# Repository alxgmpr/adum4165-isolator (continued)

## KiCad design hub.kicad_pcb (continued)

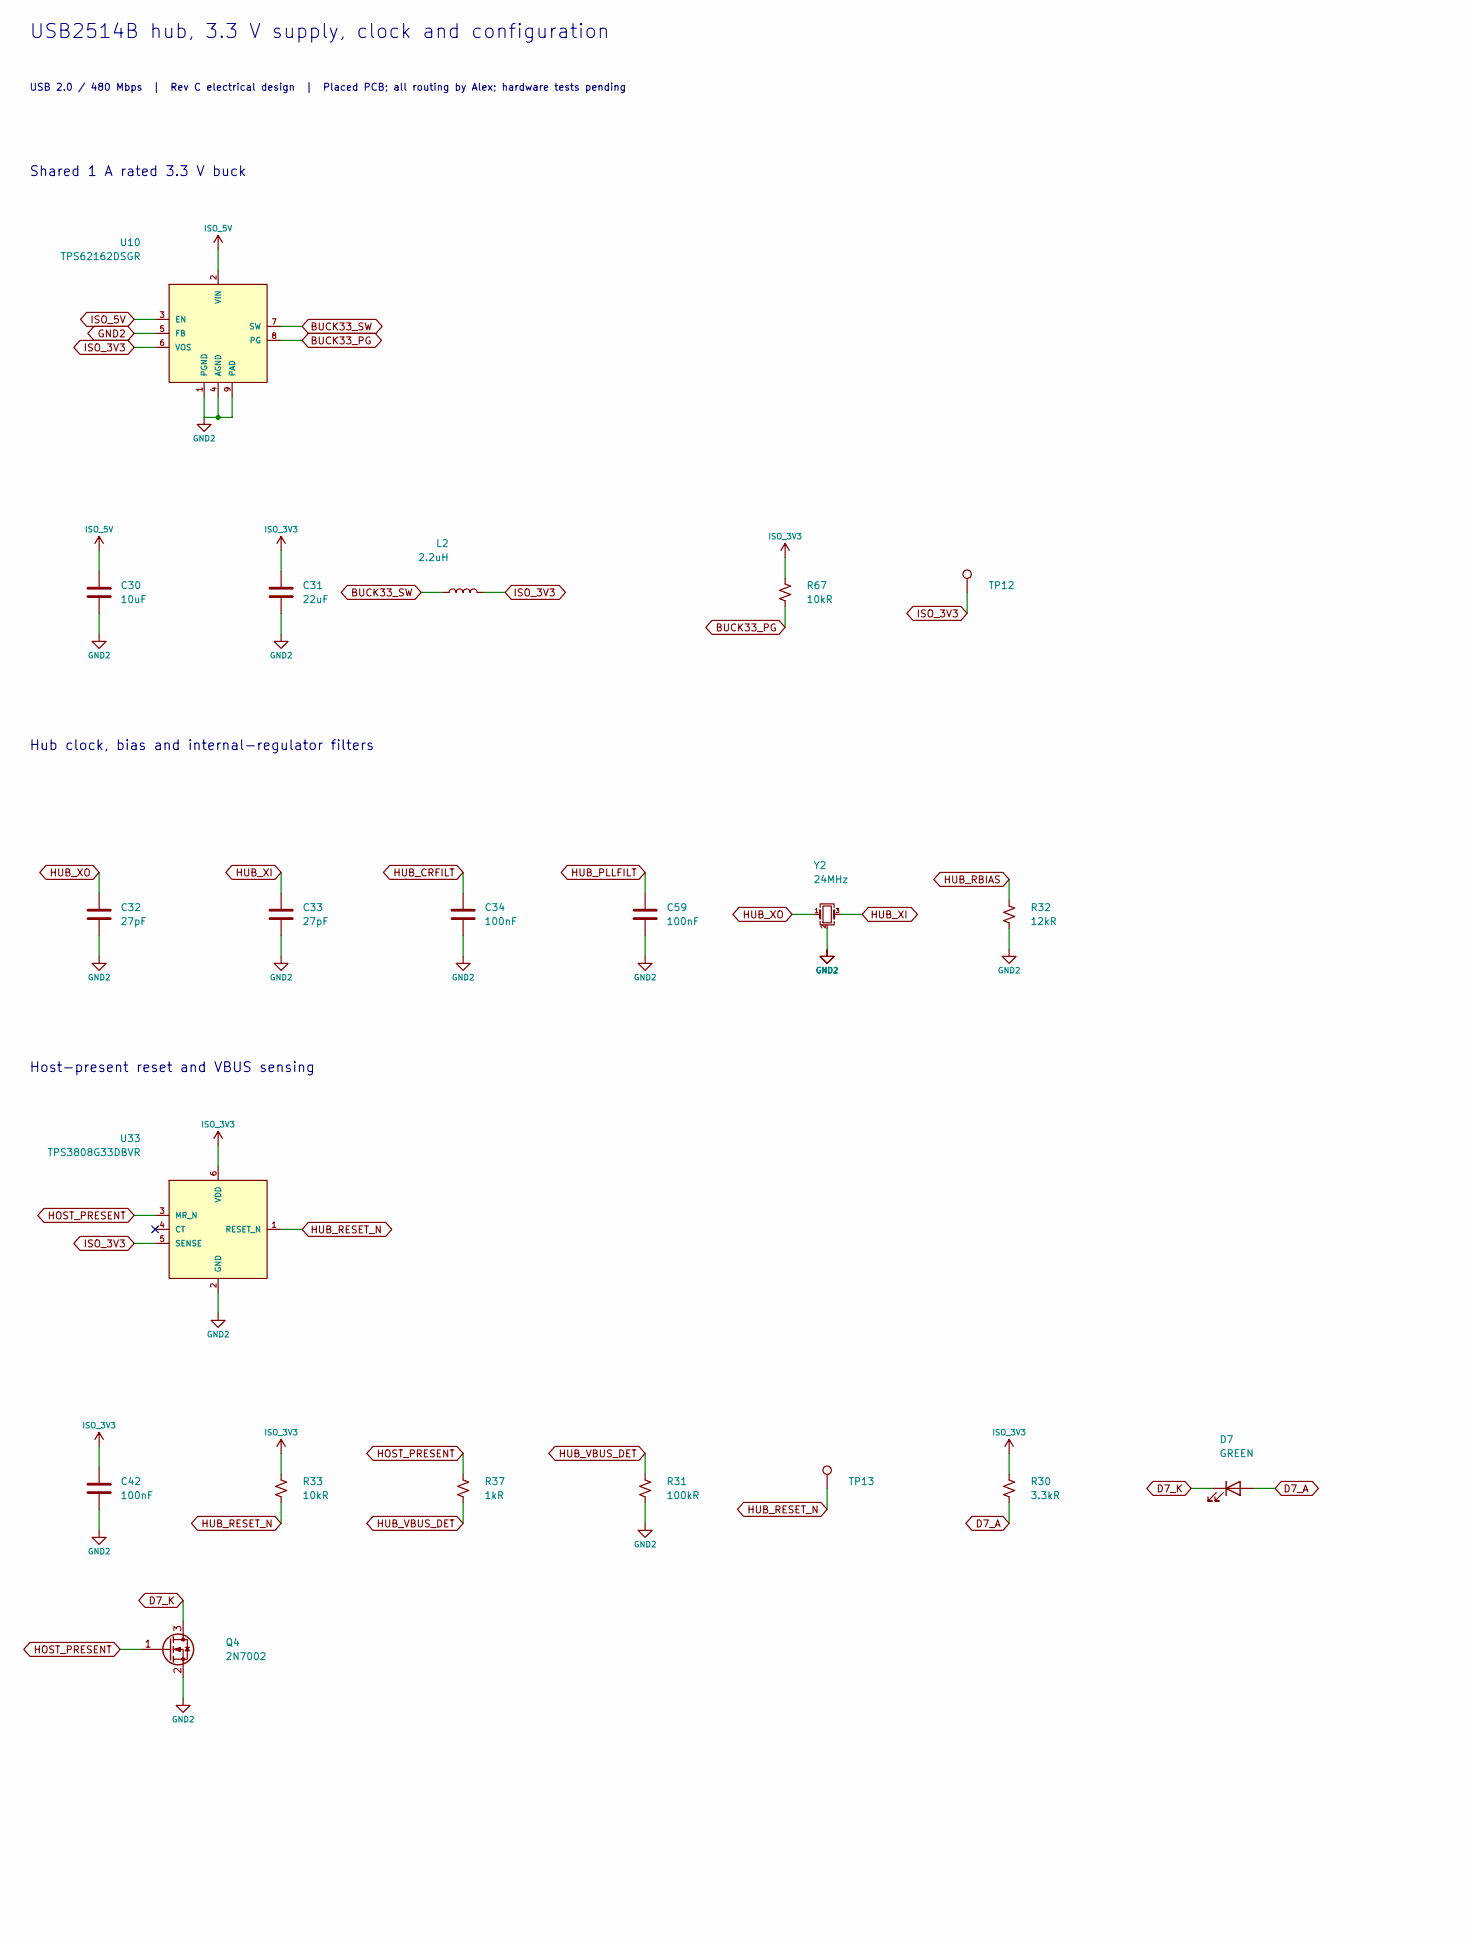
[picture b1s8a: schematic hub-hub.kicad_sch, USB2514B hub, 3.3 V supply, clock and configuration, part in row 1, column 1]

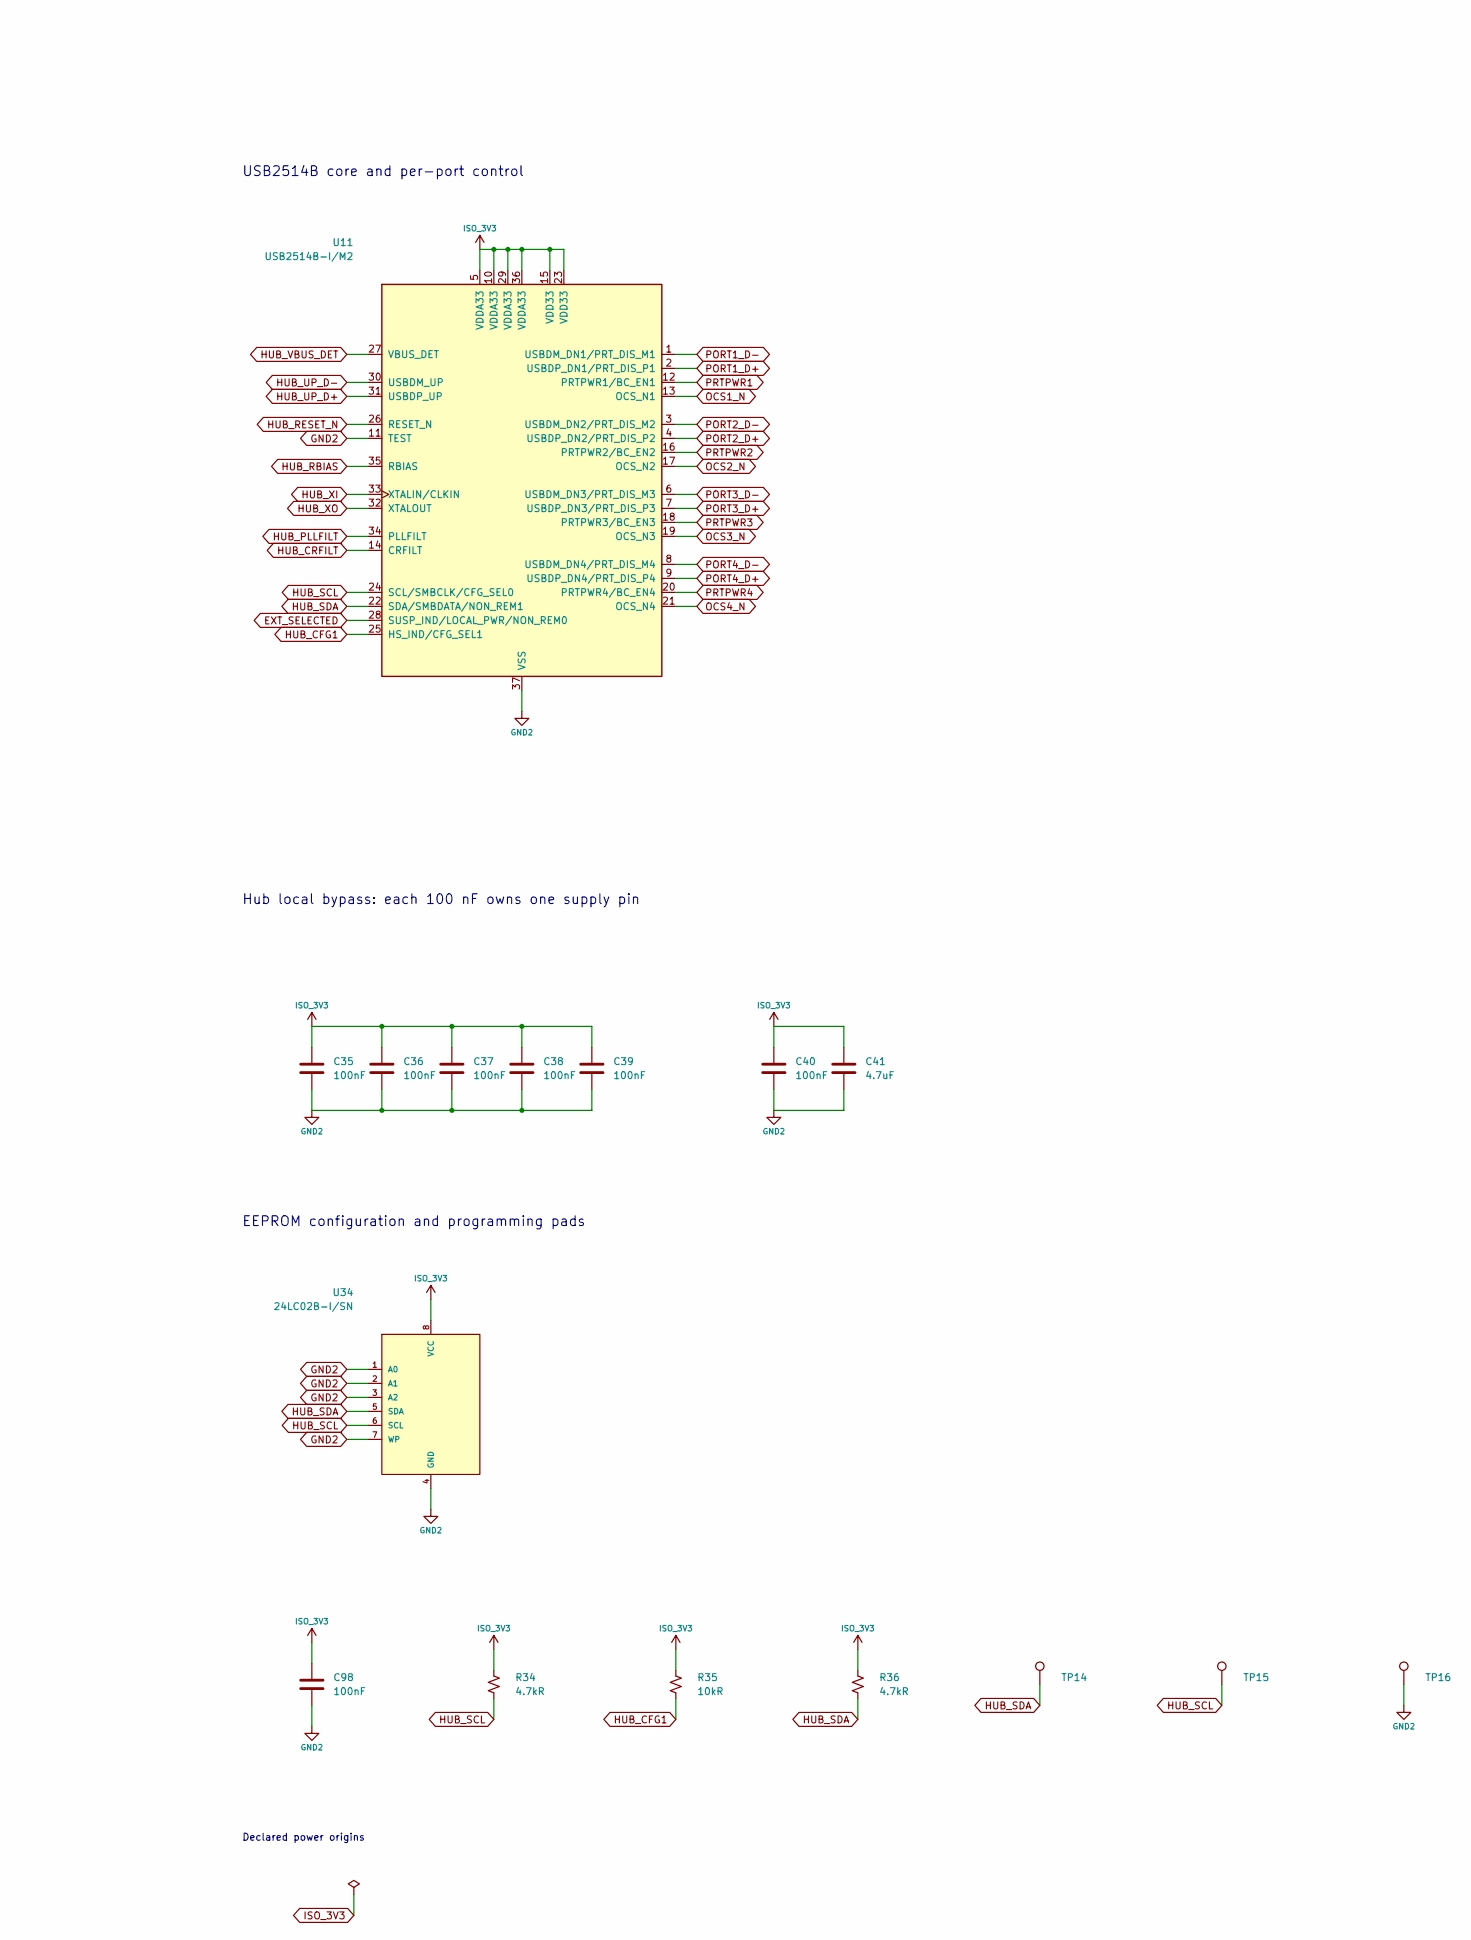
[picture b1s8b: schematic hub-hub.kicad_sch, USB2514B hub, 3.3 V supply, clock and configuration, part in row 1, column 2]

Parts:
C30: 10uF; C_0805_2012Metric; Ratings 25V X5R 10%; MPN GRM21BR61E106KA73L; LCSC C84416
C31: 22uF; C_1210_3225Metric; Ratings 25V X7R 10%; MPN GRM32ER71E226KE15L; LCSC C21397
C32, C33: 27pF; C_0402_1005Metric; Ratings 50V C0G 5%; MPN GCM1555C1H270JA16D; LCSC C126504
C34, C35, C36, C37, C38, C39, C40, C42, C59, C98: 100nF; C_0402_1005Metric; Ratings 50V X7R 10%; MPN GRM155R71H104KE14D; LCSC C77020
C41: 4.7uF; C_0603_1608Metric; Ratings 25V X5R 10%; MPN GRM188R61E475KE11D; LCSC C90057
D7: GREEN; LED_0603_1608Metric; Ratings See exact manufacturer datasheet; MPN LTST-C190KGKT; LCSC C125094
L2: 2.2uH; Coilcraft_XFL4020_4x4mm; Ratings See exact manufacturer datasheet; MPN XFL4020-222MEC; LCSC C122469
Q4: 2N7002; SOT-23; Ratings See exact manufacturer datasheet; MPN 2N7002,215; LCSC C65189
R30: 3.3kR; R_0402_1005Metric; Ratings 1%, 0.1W, 50V; MPN ERJ2RKF3301X; LCSC C409909
R31: 100kR; R_0402_1005Metric; Ratings 1%, 0.1W, 50V; MPN ERJ2RKF1003X; LCSC C192169
R32: 12kR; R_0402_1005Metric; Ratings 1%, 0.1W, 50V; MPN ERJ2RKF1202X; LCSC C413095
R33, R35, R67: 10kR; R_0402_1005Metric; Ratings 1%, 0.1W, 50V; MPN ERJ2RKF1002X; LCSC C191123
R34, R36: 4.7kR; R_0402_1005Metric; Ratings 1%, 0.1W, 50V; MPN ERJ2RKF4701X; LCSC C400631
R37: 1kR; R_0402_1005Metric; Ratings 1%, 0.1W, 50V; MPN ERJ2RKF1001X; LCSC C242161
TP12: ISO_3V3; TestPoint_Pad_D1.0mm; Ratings Exposed test pad; no purchased part
TP13: HUB_RESET_N; TestPoint_Pad_D1.0mm; Ratings Exposed test pad; no purchased part
TP14: HUB_SDA; TestPoint_Pad_D1.0mm; Ratings Exposed test pad; no purchased part
TP15: HUB_SCL; TestPoint_Pad_D1.0mm; Ratings Exposed test pad; no purchased part
TP16: GND2; TestPoint_Pad_D1.0mm; Ratings Exposed test pad; no purchased part
U10: TPS62162DSGR; Texas_DSG0008A_WSON-8-1EP_2x2mm_P0.5mm_EP0.9x1.6mm; Ratings See exact manufacturer datasheet; MPN TPS62162DSGR; LCSC C40256
U11: USB2514B-I/M2; Microchip_SQFN36_6x6mm_EP3.7mm; Ratings See exact manufacturer datasheet; MPN USB2514B-I/M2; LCSC C220679
U33: TPS3808G33DBVR; SOT-23-6; Ratings See exact manufacturer datasheet; MPN TPS3808G33DBVR; LCSC C43698
U34: 24LC02B-I/SN; SOIC-8_3.9x4.9mm_P1.27mm; Ratings See exact manufacturer datasheet; MPN 24LC02B-I/SN; LCSC C1348870
Y2: 24MHz; Crystal_SMD_3225-4Pin_3.2x2.5mm; Ratings See exact manufacturer datasheet; MPN ABM8G-24.000MHZ-18-D2Y-T; LCSC C596911

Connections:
BUCK33_PG: R67.2, U10.8 (PG)
BUCK33_SW: L2.1, U10.7 (SW)
D7_A: D7.2 (A), R30.2
D7_K: D7.1 (K), Q4.3 (D)
EXT_SELECTED: U11.28 (SUSP_IND/LOCAL_PWR/NON_REM0); also elsewhere on the board
GND2: C30.2, C31.2, C32.2, C33.2, C34.2, C35.2, C36.2, C37.2, C38.2, C39.2, C40.2, C41.2, C42.2, C59.2, C98.2, Q4.2 (S), R31.2, R32.2, TP16.1, U10.1 (PGND), U10.4 (AGND), U10.5 (FB), U10.9 (PAD), U11.11 (TEST), U11.37 (VSS), U33.2 (GND), U34.1 (A0), U34.2 (A1), U34.3 (A2), U34.4 (GND), U34.7 (WP), Y2.2 (G), Y2.4 (G); also elsewhere on the board
HOST_PRESENT: Q4.1 (G), R37.1, U33.3 (MR_N); also elsewhere on the board
HUB_CFG1: R35.2, U11.25 (HS_IND/CFG_SEL1)
HUB_CRFILT: C34.1, U11.14 (CRFILT)
HUB_PLLFILT: C59.1, U11.34 (PLLFILT)
HUB_RBIAS: R32.1, U11.35 (RBIAS)
HUB_RESET_N: R33.2, TP13.1, U11.26 (RESET_N), U33.1 (RESET_N)
HUB_SCL: R34.2, TP15.1, U11.24 (SCL/SMBCLK/CFG_SEL0), U34.6 (SCL)
HUB_SDA: R36.2, TP14.1, U11.22 (SDA/SMBDATA/NON_REM1), U34.5 (SDA)
HUB_UP_D+: U11.31 (USBDP_UP); also elsewhere on the board
HUB_UP_D-: U11.30 (USBDM_UP); also elsewhere on the board
HUB_VBUS_DET: R31.1, R37.2, U11.27 (VBUS_DET)
HUB_XI: C33.1, U11.33 (XTALIN/CLKIN), Y2.3
HUB_XO: C32.1, U11.32 (XTALOUT), Y2.1
ISO_3V3: C31.1, C35.1, C36.1, C37.1, C38.1, C39.1, C40.1, C41.1, C42.1, C98.1, L2.2, R30.1, R33.1, R34.1, R35.1, R36.1, R67.1, TP12.1, U10.6 (VOS), U11.5 (VDDA33), U11.10 (VDDA33), U11.15 (VDD33), U11.23 (VDD33), U11.29 (VDDA33), U11.36 (VDDA33), U33.5 (SENSE), U33.6 (VDD), U34.8 (VCC); also elsewhere on the board
ISO_5V: C30.1, U10.2 (VIN), U10.3 (EN); also elsewhere on the board
OCS1_N: U11.13 (OCS_N1); also elsewhere on the board
OCS2_N: U11.17 (OCS_N2); also elsewhere on the board
OCS3_N: U11.19 (OCS_N3); also elsewhere on the board
OCS4_N: U11.21 (OCS_N4); also elsewhere on the board
PORT1_D+: U11.2 (USBDP_DN1/PRT_DIS_P1); also elsewhere on the board
PORT1_D-: U11.1 (USBDM_DN1/PRT_DIS_M1); also elsewhere on the board
PORT2_D+: U11.4 (USBDP_DN2/PRT_DIS_P2); also elsewhere on the board
PORT2_D-: U11.3 (USBDM_DN2/PRT_DIS_M2); also elsewhere on the board
PORT3_D+: U11.7 (USBDP_DN3/PRT_DIS_P3); also elsewhere on the board
PORT3_D-: U11.6 (USBDM_DN3/PRT_DIS_M3); also elsewhere on the board
PORT4_D+: U11.9 (USBDP_DN4/PRT_DIS_P4); also elsewhere on the board
PORT4_D-: U11.8 (USBDM_DN4/PRT_DIS_M4); also elsewhere on the board
PRTPWR1: U11.12 (PRTPWR1/BC_EN1); also elsewhere on the board
PRTPWR2: U11.16 (PRTPWR2/BC_EN2); also elsewhere on the board
PRTPWR3: U11.18 (PRTPWR3/BC_EN3); also elsewhere on the board
PRTPWR4: U11.20 (PRTPWR4/BC_EN4); also elsewhere on the board

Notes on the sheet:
USB2514B hub, 3.3 V supply, clock and configuration
USB 2.0 / 480 Mbps | Rev C electrical design | Placed PCB; all routing by Alex; hardware tests pending
Shared 1 A rated 3.3 V buck
USB2514B core and per-port control
Hub clock, bias and internal-regulator filters
Hub local bypass: each 100 nF owns one supply pin
Host-present reset and VBUS sensing
EEPROM configuration and programming pads
Declared power origins

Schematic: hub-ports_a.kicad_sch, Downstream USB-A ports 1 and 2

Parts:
C43, C45, C46, C48: 100nF; C_0402_1005Metric; Ratings 50V X7R 10%; MPN GRM155R71H104KE14D; LCSC C77020
C44, C47: 220uF; CP_Elec_8x6.2; Ratings 220uF 10V +/-20%; 8mm diameter, 6.5mm m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; MPN EEEFK1A221P; LCSC C401648
D8, D9: T6V0S5A-7; D_SOD-523; Ratings See exact manufacturer datasheet; MPN T6V0S5A-7; LCSC C19950551
J3, J4: USB-A; USB_A_Wuerth_614004134726_Horizontal; Ratings See exact manufacturer datasheet; MPN 614004134726
R38, R39: 46.4kR; R_0402_1005Metric; Ratings 1%, 0.1W, 50V; MPN ERJ2RKF4642X; LCSC C416544
R47, R48, R101, R102: 100kR; R_0402_1005Metric; Ratings 1%, 0.1W, 50V; MPN ERJ2RKF1003X; LCSC C192169
U12, U13: TPS2553DBVR; SOT-23-6; Ratings See exact manufacturer datasheet; MPN TPS2553DBVR; LCSC C55266
U16, U17: USBLC6-2SC6; SOT-23-6; Ratings See exact manufacturer datasheet; MPN USBLC6-2SC6; LCSC C7519

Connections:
GND2: C43.2, C44.2, C45.2, C46.2, C47.2, C48.2, D8.2 (A), D9.2 (A), J3.4 (GND), J3.SH (Shield), J4.4 (GND), J4.SH (Shield), R38.2, R39.2, R101.2, R102.2, U12.2 (GND), U13.2 (GND), U16.2 (GND), U17.2 (GND); also elsewhere on the board
ISO_3V3: R47.1, R48.1; also elsewhere on the board
OCS1_N: R47.2, U12.4 (~FAULT); also elsewhere on the board
OCS2_N: R48.2, U13.4 (~FAULT); also elsewhere on the board
PORT1_D+: J3.3 (D+), U16.3 (I/O2), U16.4 (I/O2); also elsewhere on the board
PORT1_D-: J3.2 (D-), U16.1 (I/O1), U16.6 (I/O1); also elsewhere on the board
PORT1_ILIM: R38.1, U12.5 (ILIM)
PORT1_VBUS: C44.1, C45.1, D8.1 (K), J3.1 (VBUS), U12.6 (OUT), U16.5 (VBUS)
PORT2_D+: J4.3 (D+), U17.3 (I/O2), U17.4 (I/O2); also elsewhere on the board
PORT2_D-: J4.2 (D-), U17.1 (I/O1), U17.6 (I/O1); also elsewhere on the board
PORT2_ILIM: R39.1, U13.5 (ILIM)
PORT2_VBUS: C47.1, C48.1, D9.1 (K), J4.1 (VBUS), U13.6 (OUT), U17.5 (VBUS)
PORT_SUPPLY: C43.1, C46.1, U12.1 (IN), U13.1 (IN); also elsewhere on the board
PRTPWR1: R101.1, U12.3 (EN); also elsewhere on the board
PRTPWR2: R102.1, U13.3 (EN); also elsewhere on the board

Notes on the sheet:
Downstream USB-A ports 1 and 2
USB 2.0 / 480 Mbps | Rev C electrical design | Placed PCB; all routing by Alex; hardware tests pending
Port 1: USB-A, 500 mA with qualified external power
Port 2: USB-A, 500 mA with qualified external power

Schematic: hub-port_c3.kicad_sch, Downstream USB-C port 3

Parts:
C49, C51, C99, C100, C101, C102: 100nF; C_0402_1005Metric; Ratings 50V X7R 10%; MPN GRM155R71H104KE14D; LCSC C77020
C50: 10uF; C_0805_2012Metric; Ratings 25V X5R 10%; MPN GRM21BR61E106KA73L; LCSC C84416
D10: T6V0S5A-7; D_SOD-523; Ratings See exact manufacturer datasheet; MPN T6V0S5A-7; LCSC C19950551
J5: USB-C USB2.0; USB_C_Receptacle_HRO_TYPE-C-31-M-12; Ratings See exact manufacturer datasheet; MPN TYPE-C-31-M-12; LCSC C165948
Q5: 2N7002; SOT-23; Ratings See exact manufacturer datasheet; MPN 2N7002,215; LCSC C65189
R40: 46.4kR; R_0402_1005Metric; Ratings 1%, 0.1W, 50V; MPN ERJ2RKF4642X; LCSC C416544
R49, R103: 100kR; R_0402_1005Metric; Ratings 1%, 0.1W, 50V; MPN ERJ2RKF1003X; LCSC C192169
R72: 4.7kR; R_0402_1005Metric; Ratings 1%, 0.1W, 50V; MPN ERJ2RKF4701X; LCSC C400631
R73, R119: 10kR; R_0402_1005Metric; Ratings 1%, 0.1W, 50V; MPN ERJ2RKF1002X; LCSC C191123
R74: 909kR; R_0402_1005Metric; Ratings 1%, 0.1W, 50V; MPN ERJ2RKF9093X; LCSC C2085054
R81: 100R; R_0805_2012Metric; Ratings 100R 1%, 0.125W; 0.20mJ maximum design 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; MPN ERJ6ENF1000V; LCSC C193990
U14: TPS2553DBVR; SOT-23-6; Ratings See exact manufacturer datasheet; MPN TPS2553DBVR; LCSC C55266
U18: USBLC6-2SC6; SOT-23-6; Ratings See exact manufacturer datasheet; MPN USBLC6-2SC6; LCSC C7519
U20: TUSB320LAIRWBR; Texas_X2QFN-12_1.6x1.6mm_P0.4mm; Ratings See exact manufacturer datasheet; MPN TUSB320LAIRWBR; LCSC C132554
U35, U39: SN74LVC1G04DBVR; SOT-23-5; Ratings See exact manufacturer datasheet; MPN SN74LVC1G04DBVR; LCSC C7827
U37: SN74LVC1G08DBVR; SOT-23-5; Ratings See exact manufacturer datasheet; MPN SN74LVC1G08DBVR; LCSC C7666

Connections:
GND2: C49.2, C50.2, C51.2, C99.2, C100.2, C101.2, C102.2, D10.2 (A), J5.A1 (GND), J5.A12 (GND), J5.B1 (GND), J5.B12 (GND), J5.SH (SHIELD), Q5.2 (S), R40.2, R103.2, R119.2, U14.2 (GND), U18.2 (GND), U20.10 (GND), U20.11 (EN_N), U35.3 (GND), U37.3 (GND), U39.3 (GND); also elsewhere on the board
ISO_3V3: C99.1, C100.1, C101.1, C102.1, R49.1, R72.1, R73.1, U20.12 (VDD), U35.5 (VCC), U37.5 (VCC), U39.5 (VCC); also elsewhere on the board
OCS3_N: R49.2, U14.4 (~FAULT); also elsewhere on the board
PORT3_ATTACHED: U35.4, U37.2
PORT3_CC1: J5.A5 (CC1), U20.1 (CC1)
PORT3_CC2: J5.B5 (CC2), U20.2 (CC2)
PORT3_D+: J5.A6 (D+), J5.B6 (D+), U18.3 (I/O2), U18.4 (I/O2); also elsewhere on the board
PORT3_D-: J5.A7 (D-), J5.B7 (D-), U18.1 (I/O1), U18.6 (I/O1); also elsewhere on the board
PORT3_DISCHARGE: Q5.1 (G), U39.4
PORT3_DISCHARGE_D: Q5.3 (D), R81.2
PORT3_EN: R103.1, U14.3 (EN), U37.4, U39.2
PORT3_ID_N: R73.2, U20.9 (ID), U35.2
PORT3_ILIM: R40.1, U14.5 (ILIM)
PORT3_VBUS: C50.1, C51.1, D10.1 (K), J5.A4 (VBUS), J5.A9 (VBUS), J5.B4 (VBUS), J5.B9 (VBUS), R74.1, R81.1, R119.1, U14.6 (OUT), U18.5 (VBUS)
PORT3_VDET: R74.2, U20.4 (VBUS_DET)
PORT_SUPPLY: C49.1, U14.1 (IN); also elsewhere on the board
PRTPWR3: U37.1; also elsewhere on the board
U20_PORT: R72.2, U20.3 (PORT)

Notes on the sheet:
Downstream USB-C port 3
USB 2.0 / 480 Mbps | Rev C electrical design | Placed PCB; all routing by Alex; hardware tests pending
Port 3: USB-C, USB 2.0 and ESD
Attach detection: DFP, default Rp, no VCONN
Attachment AND hub permission controls VBUS
Detach discharge, including total board power loss

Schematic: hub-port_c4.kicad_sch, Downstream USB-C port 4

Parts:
C55, C57, C103, C104, C105, C106: 100nF; C_0402_1005Metric; Ratings 50V X7R 10%; MPN GRM155R71H104KE14D; LCSC C77020
C56: 10uF; C_0805_2012Metric; Ratings 25V X5R 10%; MPN GRM21BR61E106KA73L; LCSC C84416
D13: T6V0S5A-7; D_SOD-523; Ratings See exact manufacturer datasheet; MPN T6V0S5A-7; LCSC C19950551
J6: USB-C USB2.0; USB_C_Receptacle_HRO_TYPE-C-31-M-12; Ratings See exact manufacturer datasheet; MPN TYPE-C-31-M-12; LCSC C165948
Q6: 2N7002; SOT-23; Ratings See exact manufacturer datasheet; MPN 2N7002,215; LCSC C65189
R44: 46.4kR; R_0402_1005Metric; Ratings 1%, 0.1W, 50V; MPN ERJ2RKF4642X; LCSC C416544
R50, R104: 100kR; R_0402_1005Metric; Ratings 1%, 0.1W, 50V; MPN ERJ2RKF1003X; LCSC C192169
R75: 4.7kR; R_0402_1005Metric; Ratings 1%, 0.1W, 50V; MPN ERJ2RKF4701X; LCSC C400631
R76, R120: 10kR; R_0402_1005Metric; Ratings 1%, 0.1W, 50V; MPN ERJ2RKF1002X; LCSC C191123
R77: 909kR; R_0402_1005Metric; Ratings 1%, 0.1W, 50V; MPN ERJ2RKF9093X; LCSC C2085054
R82: 100R; R_0805_2012Metric; Ratings 100R 1%, 0.125W; 0.20mJ maximum design 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; MPN ERJ6ENF1000V; LCSC C193990
U15: TPS2553DBVR; SOT-23-6; Ratings See exact manufacturer datasheet; MPN TPS2553DBVR; LCSC C55266
U19: USBLC6-2SC6; SOT-23-6; Ratings See exact manufacturer datasheet; MPN USBLC6-2SC6; LCSC C7519
U21: TUSB320LAIRWBR; Texas_X2QFN-12_1.6x1.6mm_P0.4mm; Ratings See exact manufacturer datasheet; MPN TUSB320LAIRWBR; LCSC C132554
U36, U40: SN74LVC1G04DBVR; SOT-23-5; Ratings See exact manufacturer datasheet; MPN SN74LVC1G04DBVR; LCSC C7827
U38: SN74LVC1G08DBVR; SOT-23-5; Ratings See exact manufacturer datasheet; MPN SN74LVC1G08DBVR; LCSC C7666

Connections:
GND2: C55.2, C56.2, C57.2, C103.2, C104.2, C105.2, C106.2, D13.2 (A), J6.A1 (GND), J6.A12 (GND), J6.B1 (GND), J6.B12 (GND), J6.SH (SHIELD), Q6.2 (S), R44.2, R104.2, R120.2, U15.2 (GND), U19.2 (GND), U21.10 (GND), U21.11 (EN_N), U36.3 (GND), U38.3 (GND), U40.3 (GND); also elsewhere on the board
ISO_3V3: C103.1, C104.1, C105.1, C106.1, R50.1, R75.1, R76.1, U21.12 (VDD), U36.5 (VCC), U38.5 (VCC), U40.5 (VCC); also elsewhere on the board
OCS4_N: R50.2, U15.4 (~FAULT); also elsewhere on the board
PORT4_ATTACHED: U36.4, U38.2
PORT4_CC1: J6.A5 (CC1), U21.1 (CC1)
PORT4_CC2: J6.B5 (CC2), U21.2 (CC2)
PORT4_D+: J6.A6 (D+), J6.B6 (D+), U19.3 (I/O2), U19.4 (I/O2); also elsewhere on the board
PORT4_D-: J6.A7 (D-), J6.B7 (D-), U19.1 (I/O1), U19.6 (I/O1); also elsewhere on the board
PORT4_DISCHARGE: Q6.1 (G), U40.4
PORT4_DISCHARGE_D: Q6.3 (D), R82.2
PORT4_EN: R104.1, U15.3 (EN), U38.4, U40.2
PORT4_ID_N: R76.2, U21.9 (ID), U36.2
PORT4_ILIM: R44.1, U15.5 (ILIM)
PORT4_VBUS: C56.1, C57.1, D13.1 (K), J6.A4 (VBUS), J6.A9 (VBUS), J6.B4 (VBUS), J6.B9 (VBUS), R77.1, R82.1, R120.1, U15.6 (OUT), U19.5 (VBUS)
PORT4_VDET: R77.2, U21.4 (VBUS_DET)
PORT_SUPPLY: C55.1, U15.1 (IN); also elsewhere on the board
PRTPWR4: U38.1; also elsewhere on the board
U21_PORT: R75.2, U21.3 (PORT)

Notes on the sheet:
Downstream USB-C port 4
USB 2.0 / 480 Mbps | Rev C electrical design | Placed PCB; all routing by Alex; hardware tests pending
Port 4: USB-C, USB 2.0 and ESD
Attach detection: DFP, default Rp, no VCONN
Attachment AND hub permission controls VBUS
Detach discharge, including total board power loss

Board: 4 copper layers, 295 parts (0 on the bottom side), 148 nets, no tracks yet.

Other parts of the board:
H1, H2, H3, H4: M3 NPTH; MountingHole_3.2mm_M3

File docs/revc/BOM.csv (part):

"Reference","Value","MPN","Manufacturer","Footprint","LCSC","Ratings","Datasheet","DNP","QUANTITY","CoverMPN","CoverQuantity"
"C1,C4,C7,C8,C10,C12,C14,C17,C21-C23,C25-C27,C29,C34-C40,C42,C43,C45,C46,C48,C49,C51,C55,C57,C59,C62,C63,C66,C69,C72,C75,C81-C83,C89,C93-C110,C112,C117","100nF","GRM155R71H104KE14D","Murata Manufacturing","hub-lib:C_0402_1005Metric","C77020","50V X7R 10%","https://www.murata.com/en-global/products/productdetail?part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","","62","",""
"C2,C3,C24,C28,C61,C64,C77","1uF","GRM188R61E105KA12D","Murata Manufacturing","hub-lib:C_0603_1608Metric","C77046","25V X5R 10%","https://www.murata.com/en-global/products/productdetail?part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","","7","",""
"C11,C41,C65,C68,C71,C74","4.7uF","GRM188R61E475KE11D","Murata Manufacturing","hub-lib:C_0603_1608Metric","C90057","25V X5R 10%","https://www.murata.com/en-global/products/productdetail?part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","","6","",""
"C13,C15,C16,C18-C20,C31,C79,C80,C84-C88,C114,C116","22uF","GRM32ER71E226KE15L","Murata Manufacturing","hub-lib:C_1210_3225Metric","C21397","25V X7R 10%","https://www.murata.com/en-global/products/productdetail?part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","","16","",""
"C30,C50,C56","10uF","GRM21BR61E106KA73L","Murata Manufacturing","hub-lib:C_0805_2012Metric","C84416","25V X5R 10%","https://www.murata.com/en-global/products/productdetail?part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","","3","",""
"C32,C33","27pF","GCM1555C1H270JA16D","Murata Manufacturing","hub-lib:C_0402_1005Metric","C126504","50V C0G 5%","https://www.murata.com/en-global/products/productdetail?part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","","2","",""
"C44,C47,C92","220uF","EEEFK1A221P","Panasonic Industry","hub-lib:CP_Elec_8x6.2","C401648","220uF 10V +/-20%; 8mm diameter, 6.5mm maximum height; polarized","https://industrial.panasonic.com/ww/products/pt/aluminum-cap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","","3","",""
"C67,C70,C73,C76,C78","10nF","GRM155R71H103KA88D","Murata Manufacturing","hub-lib:C_0402_1005Metric","C77019","50V X7R 10%","https://www.murata.com/en-global/products/productdetail?part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","","5","",""
"C90","220nF","GRM155R71C224KA12D","Murata Manufacturing","hub-lib:C_0402_1005Metric","C77011","16V X7R 10%","https://www.murata.com/en-global/products/productdetail?part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","","1","",""
"C91","100pF","GRM1555C1H101JA01D","Murata Manufacturing","hub-lib:C_0402_1005Metric","C77177","50V C0G 5%","https://www.murata.com/en-global/products/productdetail?part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","","1","",""
"C113","4.7uF","GRM21BR61E475KA12L","Murata Manufacturing","hub-lib:C_0805_2012Metric","C77077","25V X5R 10%","https://www.murata.com/en-global/products/productdetail?part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","","1","",""
"C115","22nF","GRM155R71H223KA12D","Murata Manufacturing","hub-lib:C_0402_1005Metric","C77023","50V X7R 10%","https://www.murata.com/en-global/products/productdetail?part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","","1","",""
"CY1","1nF Y1","Q07F3Z102MA5B0S0N0","STE Songtian","hub-lib:C_Disc_D7.0mm_W5.5mm_P14.00mm","C2914611","See exact manufacturer datasheet","https://wmsc.lcsc.com/wmsc/upload/file/pdf/v2/lcsc/211109103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","","1","",""
"D1,D5,D8-D10,D13","T6V0S5A-7","T6V0S5A-7","Diodes Incorporated","hub-lib:D_SOD-523","C19950551","See exact manufacturer datasheet","https://www.diodes.com/assets/Datasheets/T6V0S5A.pdf","","6","",""
"D2,D6,D7","GREEN","LTST-C190KGKT","Lite-On","hub-lib:LED_0603_1608Metric","C125094","See exact manufacturer datasheet","https://optoelectronics.liteon.com/upload/download/DS22-2000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","","3","",""
"D3,D4","SS34","SS34","MDD Microdiode Electronics","hub-lib:D_SMA","C8678","See exact manufacturer datasheet","https://www.lcsc.com/datasheet/C8678.pdf","","2","",""
"D14-D17","BAT54WS","BAT54WS-7-F","Diodes Incorporated","hub-lib:D_SOD-323","C124205","See exact manufacturer datasheet","https://www.diodes.com/assets/Datasheets/BAT54WS.pdf","","4","",""
"D20-D23","BAT54C","BAT54C,215","Nexperia","hub-lib:SOT-23","C37704","See exact manufacturer datasheet","https://assets.nexperia.com/documents/data-sheet/BAT54_SER.pdf","","4","",""
"J1,J2,J5,J6","USB-C 5V POWER,USB-C USB2.0","TYPE-C-31-M-12","HRO","hub-lib:USB_C_Receptacle_HRO_TYPE-C-31-M-12","C165948","See exact manufacturer datasheet","https://datasheet.lcsc.com/datasheet/pdf/9e56b777c022540fcce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","","4","",""
"J3,J4","USB-A","614004134726","Wurth Elektronik","hub-lib:USB_A_Wuerth_614004134726_Horizontal","","See exact manufacturer datasheet","https://www.we-online.com/components/products/datasheet/6140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","","2","",""
"L1","1.5uH","XFL4020-152MEC","Coilcraft","hub-lib:Coilcraft_XFL4020_4x4mm","C3033018","See exact manufacturer datasheet","https://www.coilcraft.com/getmedia/50632d43-da1b-4cdb-8ab4-3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","","1","",""
"L2,L4","2.2uH","XFL4020-222MEC","Coilcraft","hub-lib:Coilcraft_XFL4020_4x4mm","C122469","See exact manufacturer datasheet","https://www.coilcraft.com/getmedia/50632d43-da1b-4cdb-8ab4-3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","","2","",""
"L3","4.7uH","XAL7070-472MEC","Coilcraft","hub-lib:L_Coilcraft_XAL7070-XXX","C3911513","See exact manufacturer datasheet","https://www.coilcraft.com/en-us/products/power/shielded-indu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","","1","",""
"Q2-Q6","2N7002","2N7002,215","Nexperia","hub-lib:SOT-23","C65189","See exact manufacturer datasheet","https://assets.nexperia.com/documents/data-sheet/2N7002.pdf","","5","",""
"R1,R16,R74,R77","909kR","ERJ2RKF9093X","Panasonic Industry","hub-lib:R_0402_1005Metric","C2085054","1%, 0.1W, 50V","https://industrial.panasonic.com/cdbs/www-data/pdf/RDA0000/A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","","4","",""
"R2,R3,R6,R17,R18,R24,R28,R33,R35,R61,R63,R66,R67,R73,R76,R83,R119,R120","10kR","ERJ2RKF1002X","Panasonic Industry","hub-lib:R_0402_1005Metric","C191123","1%, 0.1W, 50V","https://industrial.panasonic.com/cdbs/www-data/pdf/RDA0000/A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","","18","",""
"R4,R11,R12,R19,R31,R47-R50,R101-R104,R115","100kR","ERJ2RKF1003X","Panasonic Industry","hub-lib:R_0402_1005Metric","C192169","1%, 0.1W, 50V","https://industrial.panasonic.com/cdbs/www-data/pdf/RDA0000/A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","","14","",""
"R5","28.7kR","ERJ2RKF2872X","Panasonic Industry","hub-lib:R_0402_1005Metric","","1%, 0.1W, 50V","https://industrial.panasonic.com/cdbs/www-data/pdf/RDA0000/A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","","1","",""
"R9,R29,R30","3.3kR","ERJ2RKF3301X","Panasonic Industry","hub-lib:R_0402_1005Metric","C409909","1%, 0.1W, 50V","https://industrial.panasonic.com/cdbs/www-data/pdf/RDA0000/A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","","3","",""
"R10,R22,R51,R53,R55,R57,R112","0R","ERJ2GE0R00X","Panasonic Industry","hub-lib:R_0402_1005Metric","C242160","0R jumper, 0402, 1A rated current","https://industrial.panasonic.com/cdbs/www-data/pdf/RDA0000/A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","","7","",""
"R15,R52,R54,R56,R58","0R","ERJ2GE0R00X","Panasonic Industry","hub-lib:R_0402_1005Metric","C242160","0R jumper, 0402, 1A rated current","https://industrial.panasonic.com/cdbs/www-data/pdf/RDA0000/A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","DNP","5","",""
"R20,R65","10kR","RT0603BRB0710KL","Yageo","hub-lib:R_0603_1608Metric","C860067","0.1%, 10ppm/C thin film, 0.1W","https://www.yageo.com/upload/media/product/productsearch/dat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","","2","",""
"R21","3kR","RT0603BRB073KL","Yageo","hub-lib:R_0603_1608Metric","C860379","0.1%, 10ppm/C thin film, 0.1W","https://www.yageo.com/upload/media/product/productsearch/dat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","","1","",""
"R23","17.8kR","ERJ2RKF1782X","Panasonic Industry","hub-lib:R_0402_1005Metric","","1%, 0.1W, 50V","https://industrial.panasonic.com/cdbs/www-data/pdf/RDA0000/A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","","1","",""
"R25","23.7kR","ERJ2RKF2372X","Panasonic Industry","hub-lib:R_0402_1005Metric","","1%, 0.1W, 50V","https://industrial.panasonic.com/cdbs/www-data/pdf/RDA0000/A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","","1","",""
"R26","10.2kR","ERJ2RKF1022X","Panasonic Industry","hub-lib:R_0402_1005Metric","C2076944","1%, 0.1W, 50V","https://industrial.panasonic.com/cdbs/www-data/pdf/RDA0000/A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","","1","",""
"R27","29.8kR","ERJ2RKF2982X","Panasonic Industry","hub-lib:R_0402_1005Metric","","1%, 0.1W, 50V","https://industrial.panasonic.com/cdbs/www-data/pdf/RDA0000/A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","","1","",""
"R32","12kR","ERJ2RKF1202X","Panasonic Industry","hub-lib:R_0402_1005Metric","C413095","1%, 0.1W, 50V","https://industrial.panasonic.com/cdbs/www-data/pdf/RDA0000/A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","","1","",""
"R34,R36,R72,R75","4.7kR","ERJ2RKF4701X","Panasonic Industry","hub-lib:R_0402_1005Metric","C400631","1%, 0.1W, 50V","https://industrial.panasonic.com/cdbs/www-data/pdf/RDA0000/A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","","4","",""
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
